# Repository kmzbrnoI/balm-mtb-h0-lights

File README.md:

Osvětlení vozů malý Balm H0
===========================

Tento repozitář obsahuje podklady pro výrobu dekodéru osvětlení vlečných vozů
Balm firmy MTBmodel.

Osvětlení se skládá z horní desky ([pcb](pcb), montuje se pod strop vozů) a dvou
čelních desek ([pcb-head](pcb-head)) pro koncová světla. Na horní desce je procesor
PIC12F629, do kterého se nahrává firmware ze složky [fw](fw),

## Návod k použití

Návod obsahuje popis základních parametrů osvětlení.

* [Webový návod](https://docs.google.com/document/d/e/2PACX-1vRgrOjyaV_YPN3vRX59pJFN3mEdiZDsYugB_XFN0bcXFv8iJtmIPFT6zj8s5dFSr0we1PM2x35lkkI6/pub)
* [PDF](https://drive.google.com/file/d/1UF51u17YCr2_-8sSnn3kVr8-1jqHwtga/view)

## Autoři

* Autorem DPS je [Jan Horáček](mailto:jan.horacek@kmz-brno.cz).
* Autory firmwaru jsou: Paco Canada, Michal Petrilak,
  [Jan Horáček](mailto:jan.horacek@kmz-brno.cz).

## Licence

Hardware je vydán pod licencí [Creative Commons Attribution-ShareAlike 4.0
License](https://creativecommons.org/licenses/by-sa/4.0/) jako openhardware
projekt. Kdokoliv si může stáhnout data, přispět k projektu, vyrobit si vlastní
DPS nebo dokonce vyrobené DPS využít pro komerční účely.

Firmware je převzat od [Paco](https://usuaris.tinet.cat/fmco/home_en.htm)
[Function decoder with 4 outputs v.2](https://usuaris.tinet.cat/fmco/home_en.htm).

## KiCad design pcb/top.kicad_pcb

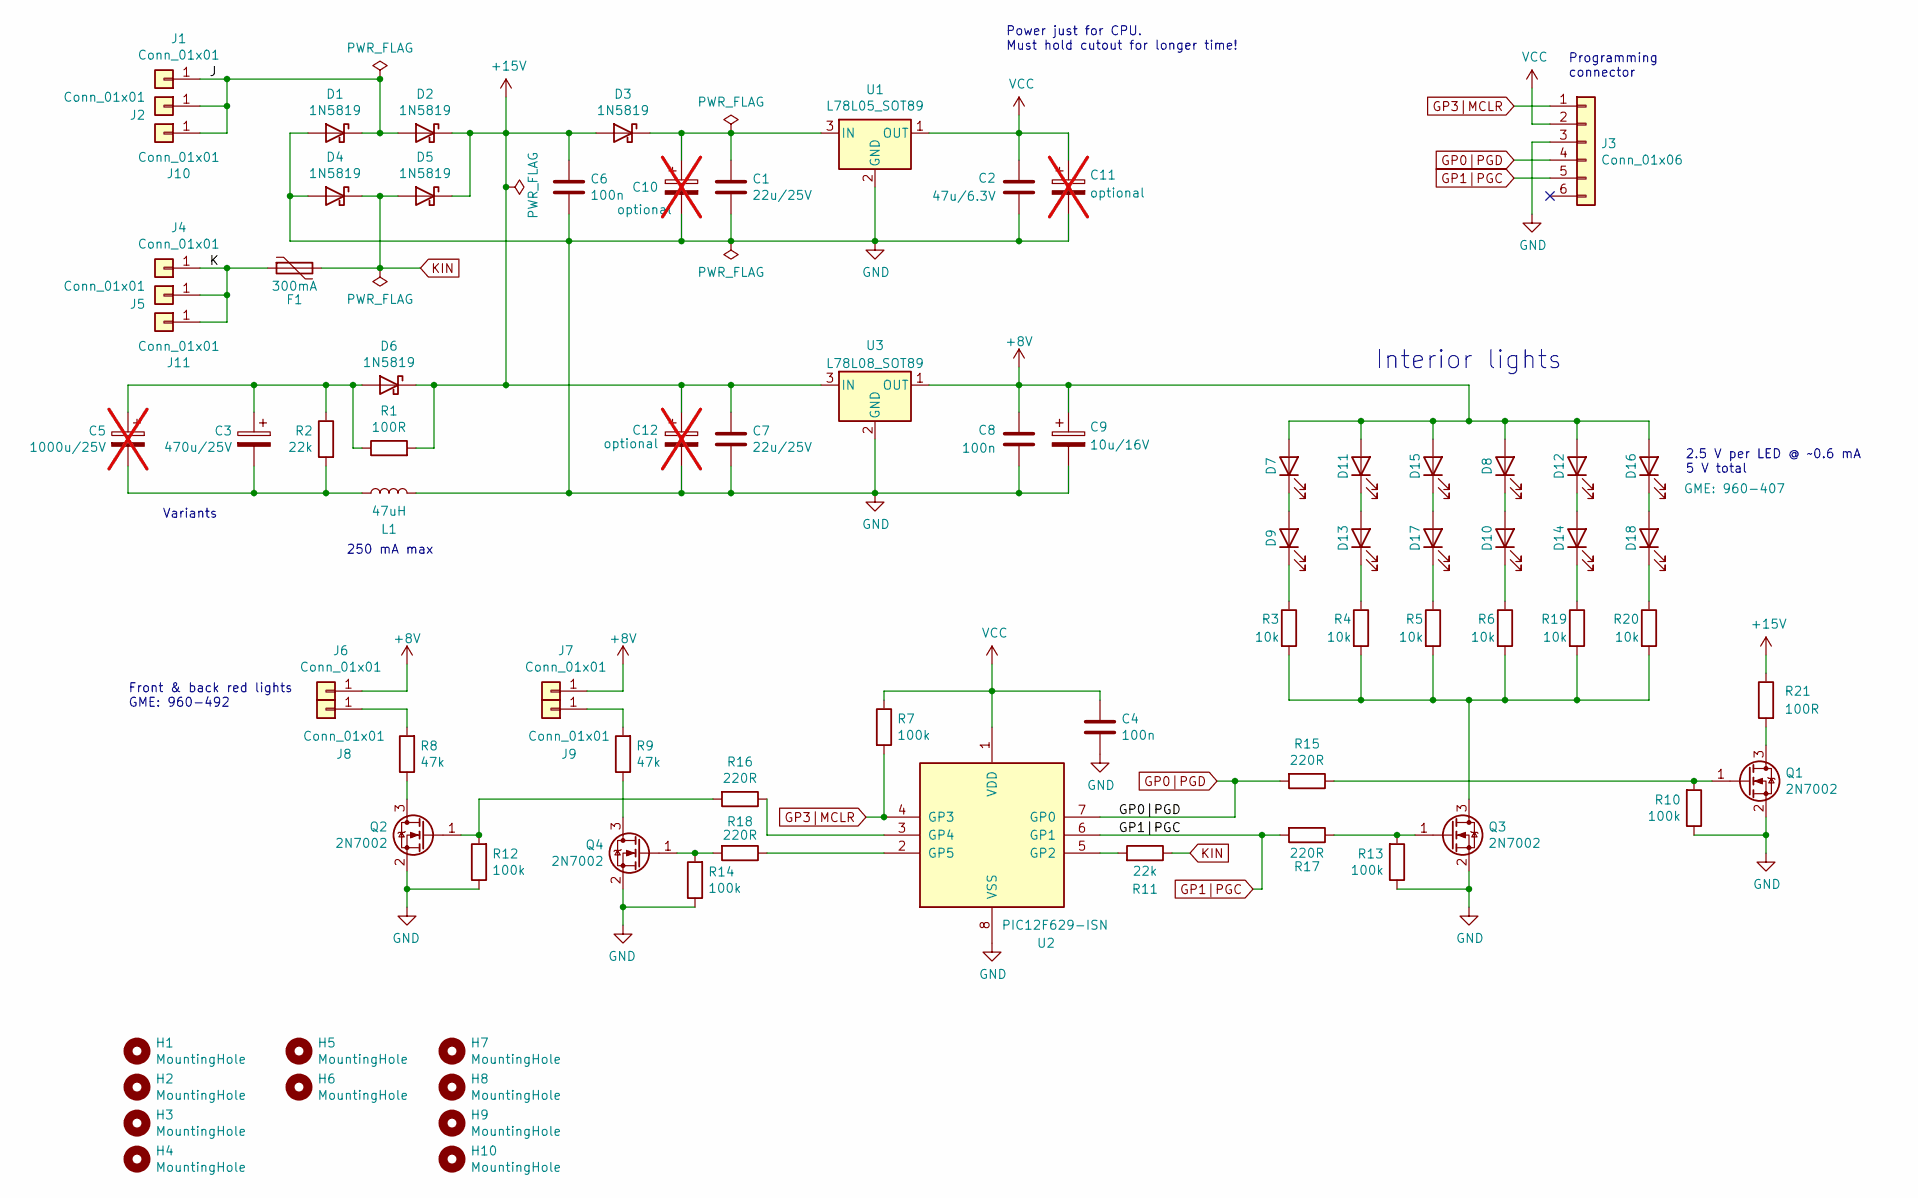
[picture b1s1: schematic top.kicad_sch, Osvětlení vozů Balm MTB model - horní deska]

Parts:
C1, C7: 22u/25V; C_0805_2012Metric_Pad1.18x1.45mm_HandSolder; LCSC C45783
C2: 47u/6.3V; C_0805_2012Metric_Pad1.18x1.45mm_HandSolder; LCSC C16780
C3: 470u/25V; CP_Radial_D8.0mm_P3.50mm; JLCPCB_IGNORE true
C4, C6, C8: 100n; C_0805_2012Metric_Pad1.18x1.45mm_HandSolder; LCSC C49678
C5: 1000u/25V; CP_Radial_D10.0mm_P5.00mm; JLCPCB_IGNORE true; not fitted
C9: 10u/16V; CP_EIA-3216-10_Kemet-I; LCSC C7171
C10, C11, C12: optional; CP_EIA-3216-10_Kemet-I; JLCPCB_IGNORE true; not fitted
D1, D2, D3, D4, D5, D6: 1N5819; D_SOD-123; LCSC C8598
D7, D8, D9, D10, D11, D12, D13, D14, D15, D16, D17, D18: LED; LED_PLCC_2835_Handsoldering; JLCPCB_IGNORE true
F1: 300mA; Fuse_1206_3216Metric_Pad1.42x1.75mm_HandSolder; LCSC C151132
H1, H2, H3, H4, H5, H6: MountingHole; MountingHole_2.7mm_M2.5; JLCPCB_IGNORE true
H7, H8, H9, H10: MountingHole; MountingHole_2.2mm_M2; JLCPCB_IGNORE true
J1, J2, J4, J5, J10, J11: Conn_01x01; PinHeader_1x01_P2.54mm_Vertical; JLCPCB_IGNORE true
J3: Conn_01x06; PinHeader_1x06_P2.54mm_Vertical; JLCPCB_IGNORE true
J6, J7, J8, J9: Conn_01x01; TestPoint_THTPad_D1.5mm_Drill0.7mm; JLCPCB_IGNORE true
L1: 47uH; L_Axial_L6.6mm_D2.7mm_P10.16mm_Horizontal_Vishay_IM-2; JLCPCB_IGNORE true
Q1, Q2, Q3, Q4: 2N7002; SOT-23_Handsoldering; LCSC C8545
R1, R21: 100R; R_2512_6332Metric_Pad1.40x3.35mm_HandSolder; LCSC C364154
R2, R11: 22k; R_0805_2012Metric_Pad1.20x1.40mm_HandSolder; LCSC C17560
R3, R4, R5, R6, R19, R20: 10k; R_0805_2012Metric_Pad1.20x1.40mm_HandSolder; LCSC C17414
R7, R10, R12, R13, R14: 100k; R_0805_2012Metric_Pad1.20x1.40mm_HandSolder; LCSC C149504
R8, R9: 47k; R_0805_2012Metric_Pad1.20x1.40mm_HandSolder; LCSC C17713
R15, R16, R17, R18: 220R; R_0805_2012Metric_Pad1.20x1.40mm_HandSolder; LCSC C17557
U1: L78L05_SOT89; SOT-89-3_Handsoldering; LCSC C71136
U2: PIC12F629-ISN; SOIC-8_3.9x4.9mm_P1.27mm; LCSC C8226
U3: L78L08_SOT89; SOT-89-3_Handsoldering; LCSC C122846

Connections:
+8V: C8.1, C9.1, D7.2 (A), D8.2 (A), D11.2 (A), D12.2 (A), D15.2 (A), D16.2 (A), J6.1, J7.1, U3.1 (OUT)
+15V: C6.1, C7.1, C12.1, D2.1 (K), D3.2 (A), D5.1 (K), D6.1 (K), R1.2, R21.1, U3.3 (IN)
/J: D1.1 (K), D2.2 (A), J1.1, J2.1, J10.1
/K: F1.1, J4.1, J5.1, J11.1
GND: C1.2, C2.2, C4.2, C6.2, C7.2, C8.2, C9.2, C10.2, C11.2, C12.2, D1.2 (A), D4.2 (A), J3.3, L1.1, Q1.2 (S), Q2.2 (S), Q3.2 (S), Q4.2 (S), R10.1, R12.1, R13.1, R14.1, U1.2 (GND), U2.8 (VSS), U3.2 (GND)
GP0|PGD: J3.4, R15.2, U2.7 (GP0)
GP1|PGC: J3.5, R17.2, U2.6 (GP1)
GP3|MCLR: J3.1, R7.2, U2.4 (GP3)
KIN: D4.1 (K), D5.2 (A), F1.2, R11.1
unnamed: C3.2, C5.2, L1.2, R2.2
unnamed: C1.1, C10.1, D3.1 (K), U1.3 (IN)
unnamed: C3.1, C5.1, D6.2 (A), R1.1, R2.1
unnamed: D7.1 (K), D9.2 (A)
unnamed: D9.1 (K), R3.1
unnamed: D8.1 (K), D10.2 (A)
unnamed: D10.1 (K), R6.1
unnamed: D11.1 (K), D13.2 (A)
unnamed: D12.1 (K), D14.2 (A)
unnamed: D13.1 (K), R4.1
unnamed: D14.1 (K), R19.1
unnamed: D15.1 (K), D17.2 (A)
unnamed: D16.1 (K), D18.2 (A)
unnamed: D17.1 (K), R5.1
unnamed: D18.1 (K), R20.1
unnamed: J8.1, R8.2
unnamed: J9.1, R9.2
unnamed: Q1.3 (D), R21.2
unnamed: Q1.1 (G), R10.2, R15.1
unnamed: Q2.3 (D), R8.1
unnamed: Q2.1 (G), R12.2, R16.2
unnamed: Q3.3 (D), R3.2, R4.2, R5.2, R6.2, R19.2, R20.2
unnamed: Q3.1 (G), R13.2, R17.1
unnamed: Q4.3 (D), R9.1
unnamed: Q4.1 (G), R14.2, R18.2
unnamed: R11.2, U2.5 (GP2)
unnamed: R16.1, U2.3 (GP4)
unnamed: R18.1, U2.2 (GP5)
VCC: C2.1, C4.1, C11.1, J3.2, R7.1, U1.1 (OUT), U2.1 (VDD)

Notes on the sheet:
Front & back red lights GME: 960-492
Power just for CPU. Must hold cutout for longer time!
250 mA max
Interior lights
Programming connector
Variants
2.5 V per LED @ ~0.6 mA 5 V total

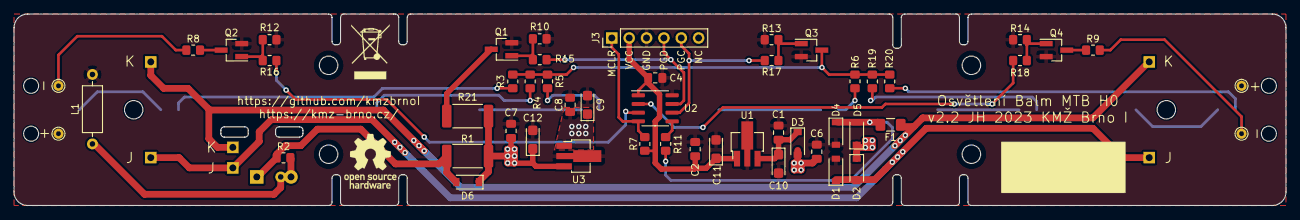
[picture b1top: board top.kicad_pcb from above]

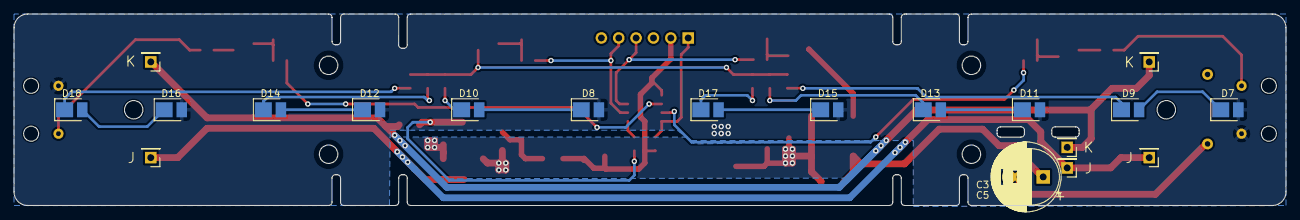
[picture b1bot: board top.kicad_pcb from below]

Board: 2 copper layers, 186.0 x 28.0 mm, 81 parts (20 on the bottom side), 38 nets.

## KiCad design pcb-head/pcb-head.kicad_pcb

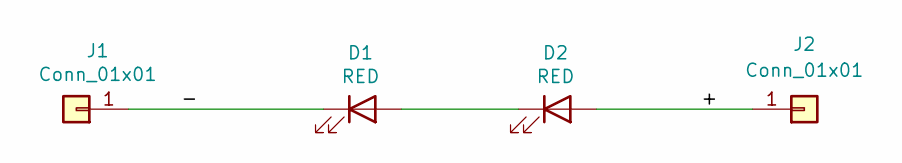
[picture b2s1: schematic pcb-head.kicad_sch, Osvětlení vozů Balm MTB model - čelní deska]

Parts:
D1, D2: RED; LED_0805_2012Metric_Pad1.15x1.40mm_HandSolder
J1, J2: Conn_01x01; TestPoint_THTPad_D1.5mm_Drill0.7mm

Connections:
/+: D2.2 (A), J2.1
/-: D1.1 (K), J1.1
unnamed: D1.2 (A), D2.1 (K)

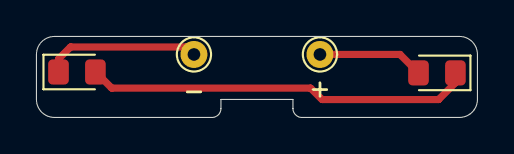
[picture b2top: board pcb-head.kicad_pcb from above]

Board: 2 copper layers, 24.5 x 4.5 mm, 4 parts (0 on the bottom side), 3 nets.

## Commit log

2021-12-23 Add pcb project.
2021-12-23 Add schematics.
2021-12-23 Add programming connector.
2021-12-24 Add clear footprints.
2021-12-24 Use discrete-parts rectifier.
2021-12-27 Annotate schematics.
2021-12-27 Add pcb outline.
2021-12-27 Add LEDs package, position LEDs.
2021-12-29 Add MOSFET gate protection resistors.
2022-01-01 Add proper PCB dimensions.
2022-01-01 Wire part of PCB.
2022-01-06 Wire whole PCB.
2022-01-06 Tweak silkscreen etc.
2022-01-06 Add LCSC.
2022-01-06 Add JLCPCB fabrication Makefile.
2022-01-06 Apply minor fabrication corrections.
2022-01-06 Use 2512 power resistor.
2022-01-13 Note LED voltage.
2022-01-13 Add head pcb schematics.
2022-01-13 Head: add pcb dimensions & basic positions.
2022-01-19 Wire head pcb.
2022-01-19 Top: switch +-.
2022-01-19 Head: add panelization Makefile.
2022-01-20 Migrate to KiCad 6.
2022-01-20 Add proper mousebites position.
2022-01-20 Remove wire stubs.
2022-01-20 fab: add --no-drc.
2022-01-20 Minor enhancements to Makefile.
2022-01-20 Add OSHW logo.
2022-02-08 Enlarge panel spacing for jlcpcb production.
2022-03-03 Top: add 100n capacitor on input.
    To filter DCC edges (causing transistors to open).
2022-03-03 Change front transistors 10k → 47k.
2022-03-03 Add firmware.
2022-03-04 Change capacitor-discharge resistor to 22k.
2022-03-04 Use schottky diodes on rectifier & capacitor.
2022-03-04 Reposition corridor LEDs to be in the middle of corridor.
2022-03-04 Change order of LEDs to 2-2-2-2-2-2.
2022-03-04 Add load resistor for CV reading.
2022-03-04 Use 8V stabilized for LEDs.
    To keep LEDs longer running on capacitor while maintaining brightness.
2022-03-04 Tweak silkscreen.
2022-03-06 Add holes for wires.
2022-03-06 Add oshw & weee logos.
2022-04-10 Sch: do not put global labels directly on corner.
    Minor schematic tweak to look better.
2022-04-16 Update fuses.
2022-04-16 Diallow to set GP0 as function output.
2023-03-15 Upgrade to newer version of firmware (FW used in MP's function decoder).
2023-03-15 Remove spaces at end-of-line.
2023-03-15 Fix fuses.
2023-03-15 Set default CV values.
2023-03-17 Change PCB color to white.
2023-03-18 Add optinal tantalum capacitor.
2023-03-18 Add JLCPCB_IGNORE or LCSC number.
2023-03-18 Use SOT89 for 78L08.
2023-03-19 Correct JLCPCB parts orientation.
2023-03-19 Add root README.
2023-03-19 Fix README.
2023-03-19 Remove old doc.
2023-03-26 Mounting holes: decrease clearance.
    Big clearance is not required, screws are small.
2023-03-31 Enalarge interior LEDs resistors to 4k7.
    Light wa too bright.
2023-04-07 Add fuse on input.
2023-06-13 Use 1N5819 insteas on 1N4148.
2023-06-13 Add optional tantalum capacitors.
2023-12-19 Add thermal relief to U1 & U3.
2023-12-19 pcbv2.2.
2023-12-23 gitignore: add .lck files.
2023-12-23 Mark unused capacitors as DNP.
2023-12-23 Update to KiCad 7.
2023-12-23 Connect CPU input after fuse.
2023-12-23 sch: update interior LEDs current, add notes.
2023-12-23 F1: fuse -> polyfuse, 500mA -> 300mA.
2023-12-24 Add silkscreen rectangle for serial number.
2024-04-16 Fix R20 name & value order.
2024-04-17 Use 10k resistors for interior LEDs instead of 4k7.
    Based on field testing.

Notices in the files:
pcb-head/pcb-head.kicad_sch:
Released under the Creative Commons Attribution-ShareAlike 4.0 License
